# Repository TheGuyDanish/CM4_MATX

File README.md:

# CM4 MATX

## This project has been archived.

Due to a few different reasons, I have decided to archive this project. There's a few different reasons, but mainly that I don't think the CM4 is an appropriate platform for this kind of board. The CPU doesn't really have enough power to utilize the kind of IO that this board would provide it with, combined with the different limitations of using PCI-e switches. This, combined with the fact that I don't have as much time as I'd like to spend on this project, I've decided to leave it be for now.

I'm not aware at the time of writing of any similar projects, but I'll be leaving this one up for folks to take resources and inspiration from.

The original readme is below for archival purposes. So long, thanks for all the fish, and may you have the best of luck in your projects!

/TheGuyDanish

<hr />

Welcome! CM4 MATX is a project aiming to create an open source, micro-ATX standard-compliant motherboard for the Raspberry Pi Compute Module 4.

<p align="center"></p>

The intent behind this is to provide a motherboard that can be installed in a regular case, as well as provide more, or easier access to, potential IO, as well as using a standard 24-pin ATX power supply. This project uses much of the CM4 IO board as its reference design, with new features added onto the board.

The current design goals are as follows:
* Use a standard mATX form factor (244*244mm) and mounting holes
* Provide dual rear-panel USB ports via USB2514B/M2 USB Hub
* Provide an internal USB expansion header for front-panel USB ports
* Provide a standard gigabit Ethernet interface for the rear panel
* Provide stacked dual HDMI outputs on the rear panel
* Provide stacked dual HDMI inputs on the rear panel, with the aid of the Toshiba TC358743 CSI2-to-HDMI bridge IC
* Where reasonably possible, expose the dual DSI headers
* Provide rear-panel acess to other RPI staples, such as SD card and 40-pin GPIO headers
* Via the PI7C9X2G404SL PCI-e switch IC, provide three lanes of PCI-e Gen 2.0 to host multiple expansion cards. These will be x16 slots, wired x1 electrically, to reduce the need for adapters
* Via the PI3PCIE2215 PCI-e mux IC, offer the user the choice between a physical PCI-e slot, or an NVMe slot using one of the downstream PCI-e lanes from the above switch.

# Help Wanted

Update: We have reached a state where we feel comfortable beginning to route the different features of the board. If you have experience with routing PCBs, you are very welcome to download the Kicad files and have a look for yourself. If you have any questions, feel free to join us on Discord if you have any questions and would like to reach out to me directly!

I (TheGuyDanish) am not an experienced board designer, nor a whiz at electronic schematics. That's why I am posting this to Github. I'd love for other hobbyists to join this project. Not just to correct my inevitable mistakes, but also to suggest new features that would make this board even better.

For technical specifics, the KiCad project was made in version 5.1.8 stable. All components not found in the standard KiCad library are included in the CM4_MATX.pretty folder (PCB footprints) and CM4_MATX.lib (schematic symbols) file.

Please see CONTRIBUTING.md for more information!

If you have the technical skills to improve this schematic, I do implore you to make a copy of the repository, make your changes and submit them in a pull request.

If you have ideas you would like to add to the design goals, please submit them in an issue so they can be discussed.

Lastly, huge thanks to volkertb, UnKnoWn-Consortium, mo-g and geerlingguy for the discussion of this in https://github.com/geerlingguy/raspberry-pi-pcie-devices/issues/19 that spawned this effort.

# License

NOTE: Some models, schematics, and/or footprints, are provided by individual manufacturers. As such, all terms and conditions for use, as well as licensing, falls to these original manufacturers. For more information, please inquire with the original component manufacturer or raise an issue here.

Copyright Oliver Møller/[@TheGuyDanish](https://github.com/TheGuyDanish) 2020.

This source describes Open Hardware and is licensed under the CERN-OHL-P v2

You may redistribute and modify this documentation and make products
using it under the terms of the CERN-OHL-P v2 (https:/cern.ch/cern-ohl).
This documentation is distributed WITHOUT ANY EXPRESS OR IMPLIED
WARRANTY, INCLUDING OF MERCHANTABILITY, SATISFACTORY QUALITY
AND FITNESS FOR A PARTICULAR PURPOSE. Please see the CERN-OHL-P v2
for applicable conditions

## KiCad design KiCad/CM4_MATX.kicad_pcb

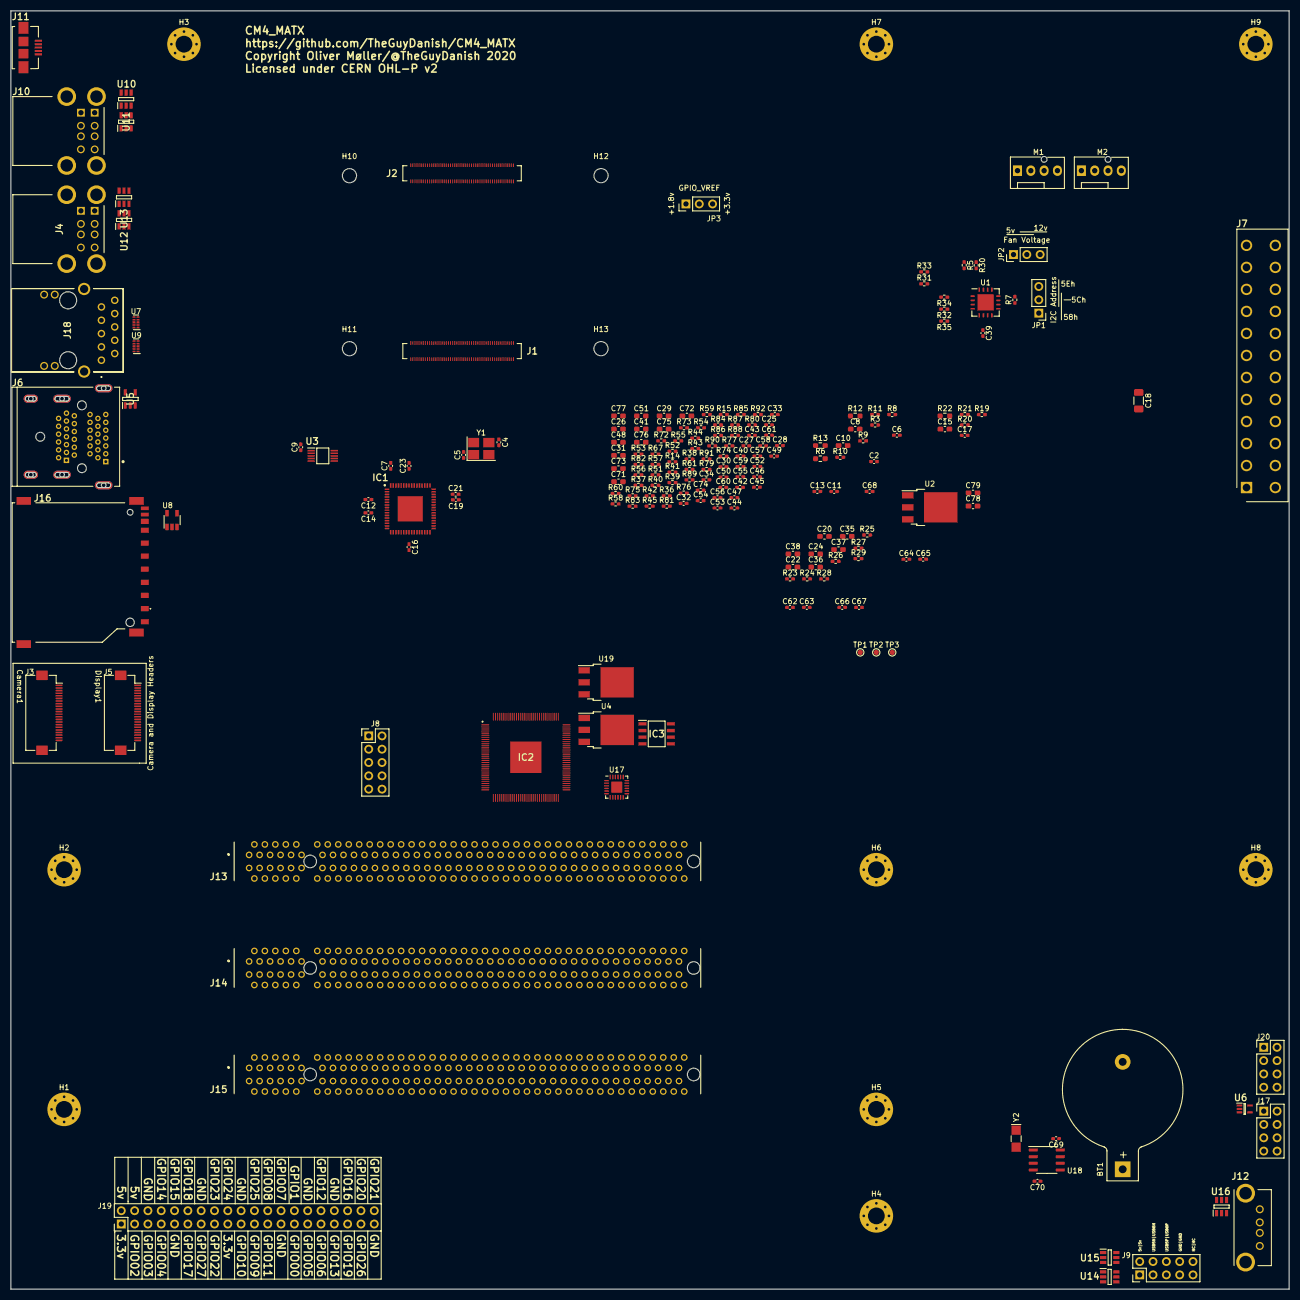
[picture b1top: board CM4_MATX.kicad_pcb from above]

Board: 4 copper layers, 243.8 x 243.8 mm, 214 parts (0 on the bottom side), 283 nets, no tracks yet.

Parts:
BT1: Battery_Cell; BatteryHolder_Keystone_103_1x20mm
C2, C6, C7, C9, C11, C12, C13, C14, C16, C17, C19, C21, C23, C25, C27, C28, C30, C32, C33, C34, C39, C40, C42, C43, C44, C45, C46, C47, C49, C50, C52, C53, C54, C55, C56, C57, C58, C59, C60, C61, C62, C63, C64, C65, C66, C67, C68, C69, C70, C74: 100nF; C_0402_1005Metric_Pad0.74x0.62mm_HandSolder
C4, C5: 16pF; C_0402_1005Metric_Pad0.74x0.62mm_HandSolder
C8, C10, C15, C20, C22, C24, C26, C29, C31, C35, C36, C37, C38, C41, C48, C51, C71, C72, C73, C75, C76, C77, C78, C79: 10uF; C_0603_1608Metric_Pad1.08x0.95mm_HandSolder
C18: 100uF; C_1206_3216Metric_Pad1.33x1.80mm_HandSolder
H1, H2, H3, H4, H5, H6, H7, H8, H9: MountingHole; MountingHole_3.2mm_M3_Pad_Via
H10, H11, H12, H13: MountingHole; MountingHole_2.7mm_M2.5
IC1: USB2517-JZX; QFN50P900X900X100-65N-D
IC2: PI7C9X2G404SLBFDE; QFP40P1600X1600X160-129N
IC3: M24C04-RMN6TP; SOIC127P600X175-8N
J1: CM4_B; DF40C100DS04V51_B
J2: CM4_A; DF40C100DS04V51
J3, J5: Conn_01x22_Female; Hirose_FH12-22S-0.5SH_1x22-1MP_P0.50mm_Horizontal
J4, J10: 72309-8014BLF; 723098014BLF
J6: 1888811-1; TE_1888811-1
J7: 39-28-1243; SHDR24W125P550X420_2X12_5160X960X1310P
J8, J9: Conn_02x05_Odd_Even; PinHeader_2x05_P2.54mm_Vertical
J11: 10104110-0001LF; 101041100001LF
J12: SS-52100-002; SS52100002
J13, J14, J15: PCIe_x16; 10018783-10113TLF
J16: GSD090012SEU
J17, J20: Conn_02x04_Odd_Even; PinHeader_2x04_P2.54mm_Vertical
J18: ARJM11C7-502-AB-ER2-T; ARJM11C7502ABER2T
J19: Conn_02x20_Odd_Even; PinHeader_2x20_P2.54mm_Vertical
JP1, JP2, JP3: Jumper_3_Open; PinHeader_1x03_P2.54mm_Vertical
M1, M2: Fan_CPU_4pin; FanPinHeader_1x04_P2.54mm_Vertical
R3, R8, R9, R10, R11: 100K 5%; R_0402_1005Metric_Pad0.72x0.64mm_HandSolder
R5, R7, R30, R31, R32, R33, R34, R35: 4.7K; R_0402_1005Metric_Pad0.72x0.64mm_HandSolder
R6, R22: 12K 1%; R_0603_1608Metric_Pad0.98x0.95mm_HandSolder
R12, R13: 2.2K 1%; R_0603_1608Metric_Pad0.98x0.95mm_HandSolder
R14: 475 1%; R_0402_1005Metric_Pad0.72x0.64mm_HandSolder
R15: 1.43k 1%; R_0402_1005Metric_Pad0.72x0.64mm_HandSolder
R19: 1K 1%; R_0402_1005Metric_Pad0.72x0.64mm_HandSolder
R20, R21: 470 1%; R_0402_1005Metric_Pad0.72x0.64mm_HandSolder
R23, R24, R25, R26, R27, R28, R29: 143 1%; R_0402_1005Metric_Pad0.72x0.64mm_HandSolder
R36, R37, R38, R39, R40, R73, R74, R75, R76, R77, R79, R80, R81, R82: 330; R_0402_1005Metric_Pad0.72x0.64mm_HandSolder
R41, R42, R43, R44, R45, R51, R52, R53, R67, R72, R91, R92: 5.1k; R_0402_1005Metric_Pad0.72x0.64mm_HandSolder
R54, R55, R56, R57, R58, R59, R60, R61: 33; R_0402_1005Metric_Pad0.72x0.64mm_HandSolder
R83, R84, R85, R86, R87, R88, R89, R90: 49.9; R_0402_1005Metric_Pad0.72x0.64mm_HandSolder
TP1: STATUS2; TestPoint_Pad_D1.0mm
TP2: STATUS0; TestPoint_Pad_D1.0mm
TP3: STATUS1; TestPoint_Pad_D1.0mm
U1: MAX6639ATE+; TQFN-16-1EP_5x5mm_P0.8mm_EP3.1x3.1mm
U2: AP7363-33D; TO-252-3_TabPin2
U3: FSUSB42MUX; SOP50P490X110-10N
U4, U19: AP7363-10D; TO-252-3_TabPin2
U5: AP2822CKETR-G1; SOT95P282X145-5N
U6: 74LVC1G07GW; SOT65P212X110-5N
U7, U9: TPD4EUSB30; USON-10_2.5x1.0mm_P0.5mm
U8: RT9742GGJ5; TSOT-23-5
U10, U11, U12, U13, U14, U15, U16: MIC2019YM6-TR; SOT95P280X145-6N
U17: TCA9548ARGER; Texas_RGE0024C_EP2.1x2.1mm
U18: PCF85263AT; SO-8_3.9x4.9mm_P1.27mm
Y1: 24MHz; Crystal_SMD_3225-4Pin_3.2x2.5mm_HandSoldering
Y2: 32.768KHz; Crystal_SMD_MicroCrystal_CC7V-T1A-2Pin_3.2x1.5mm_HandSolder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

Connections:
+3.3VA: C51.1, C57.1, C76.1, C79.1, IC2.15, J13.B10, J14.B10, J15.B10, U2.3, U19.1
+3.3VP: C68.1, J8.1, J13.A9, J13.A10, J13.B8, J14.A9, J14.A10, J14.B8, J15.A9, J15.A10, J15.B8, U17.21
+3V3: C7.1, C8.1, C9.1, C10.1, C12.1, C14.1, C16.1, C19.1, C21.1, C23.1, C26.1, C29.1, C32.1, C39.1, C40.1, C41.1, C44.1, C45.1, C48.1, C49.1, C50.1, C55.1, C56.1, C58.1, C72.1, C74.1, IC1.5, IC1.10, IC1.24, IC1.52, IC1.57, IC1.64, IC2.1, IC2.8, IC2.49, IC2.64, IC2.79, IC2.82, IC2.84, IC2.96, IC2.113, IC3.8, J3.22, J5.22, J7.2, J7.12, J7.13, JP1.3, R7.2, R32.2, R34.2, R35.2, R41.2, R42.2, R43.2, R44.2, R45.2, R51.1, R52.1, R53.1, R67.2, R72.2, R91.1, R92.1, U1.6, U3.1, U4.1
+12P: J13.A2, J13.A3, J13.B1, J13.B2, J13.B3, J14.A2, J14.A3, J14.B1, J14.B2, J14.B3, J15.A2, J15.A3, J15.B1, J15.B2, J15.B3
+12V: J7.10, J7.11, JP2.3
/+5v: C11.1, C18.1, C20.1, C22.1, C24.1, C35.1, C36.1, C37.1, C38.1, C69.1, J2.77, J7.4, J7.6, J7.21, J7.22, J7.23, J19.2, J19.4, JP2.1, U5.4, U5.5, U10.1, U11.1, U12.1, U13.1, U14.1, U15.1, U16.1, U18.8
/+5vSB: C78.1, J7.9, U2.1
/CAM_GPIO: J2.97, J3.17
/CM4_GPIO/+1.8v: J2.88, J2.90, JP3.1
/CM4_GPIO/+3.3v: J2.84, J2.86, J18.L1, J18.L3, J19.1, J19.17, JP3.3, R22.1, U6.5, U8.5
/CM4_GPIO/BT_nDis: J2.91, J20.3
/CM4_GPIO/EEPROM_nWP: J2.20, J20.7
/CM4_GPIO/ETH_LEDG: J2.15, R20.1
/CM4_GPIO/ETH_LEDY: J2.17, R21.1
/CM4_GPIO/FP_PLED: R19.1, U6.4
/CM4_GPIO/GPIO2: J2.58, J19.3
/CM4_GPIO/GPIO3: J2.56, J19.5
/CM4_GPIO/GPIO4: J2.54, J19.7
/CM4_GPIO/GPIO5: J2.34, J19.29
/CM4_GPIO/GPIO6: J2.30, J19.31
/CM4_GPIO/GPIO7: J2.37, J19.26
/CM4_GPIO/GPIO8: J2.39, J19.24
/CM4_GPIO/GPIO9: J2.40, J19.21
/CM4_GPIO/GPIO10: J2.44, J19.19
/CM4_GPIO/GPIO11: J2.38, J19.23
/CM4_GPIO/GPIO12: J2.31, J19.32
/CM4_GPIO/GPIO13: J2.28, J19.33
/CM4_GPIO/GPIO14: J2.55, J19.8
/CM4_GPIO/GPIO15: J2.51, J19.10
/CM4_GPIO/GPIO16: J2.29, J19.36
/CM4_GPIO/GPIO17: J2.50, J19.11
/CM4_GPIO/GPIO18: J2.49, J19.12
/CM4_GPIO/GPIO19: J2.26, J19.35
/CM4_GPIO/GPIO20: J2.27, J19.38
/CM4_GPIO/GPIO21: J2.25, J19.40
/CM4_GPIO/GPIO22: J2.46, J19.15
/CM4_GPIO/GPIO23: J2.47, J19.16
/CM4_GPIO/GPIO24: J2.45, J19.18
/CM4_GPIO/GPIO25: J2.41, J19.22
/CM4_GPIO/GPIO26: J2.24, J19.37
/CM4_GPIO/GPIO27: J2.48, J19.13
/CM4_GPIO/PI_nLED_ACT: J2.21, J17.3
/CM4_GPIO/RUN_PG: J2.92, J17.7
/CM4_GPIO/SD_CLK: J2.57, J16.5
/CM4_GPIO/SD_CMD: J2.62, J16.2
/CM4_GPIO/SD_DAT0: J2.63, J16.7
/CM4_GPIO/SD_DAT1: J2.67, J16.8
/CM4_GPIO/SD_DAT2: J2.69, J16.9
/CM4_GPIO/SD_DAT3: J2.61, J16.1
/CM4_GPIO/SD_DET: J2.76, J16.10
/CM4_GPIO/SD_PWR: C15.1, J16.4, U8.1
/CM4_GPIO/SD_PWR_ON: J2.75, R22.2, U8.4
/CM4_GPIO/TRD0_N: J2.10, J18.2, U7.4
/CM4_GPIO/TRD0_P: J2.12, J18.1, U7.5
/CM4_GPIO/TRD1_N: J2.6, J18.4, U7.2
/CM4_GPIO/TRD1_P: J2.4, J18.3, U7.1
/CM4_GPIO/TRD2_N: J2.9, J18.8, U9.4
/CM4_GPIO/TRD2_P: J2.11, J18.7, U9.5
/CM4_GPIO/TRD3_N: J2.5, J18.10, U9.2
/CM4_GPIO/TRD3_P: J2.3, J18.9, U9.1
/CM4_GPIO/WL_nDis: J2.89, J20.1
/CM4_GPIO/nPWR_LED: J2.95, U6.2
/CM4_GPIO/nRPIBOOT: J2.93, J20.5
/CM4_HighSpeed/CAM1_C_N: J1.127, J3.8
/CM4_HighSpeed/CAM1_C_P: J1.129, J3.9
/CM4_HighSpeed/CAM1_D0_N: J1.115, J3.2
/CM4_HighSpeed/CAM1_D0_P: J1.117, J3.3
/CM4_HighSpeed/CAM1_D1_N: J1.121, J3.5
/CM4_HighSpeed/CAM1_D1_P: J1.123, J3.6
/CM4_HighSpeed/CAM1_D2_N: J1.133, J3.11
/CM4_HighSpeed/CAM1_D2_P: J1.135, J3.12
/CM4_HighSpeed/CAM1_D3_N: J1.139, J3.14
/CM4_HighSpeed/CAM1_D3_P: J1.141, J3.15
/CM4_HighSpeed/DSI1_C_N: J1.187, J5.8
/CM4_HighSpeed/DSI1_C_P: J1.189, J5.9
/CM4_HighSpeed/DSI1_D0_N: J1.175, J5.2
/CM4_HighSpeed/DSI1_D0_P: J1.177, J5.3
/CM4_HighSpeed/DSI1_D1_N: J1.181, J5.5
/CM4_HighSpeed/DSI1_D1_P: J1.183, J5.6
/CM4_HighSpeed/DSI1_D2_N: J1.193, J5.11
/CM4_HighSpeed/DSI1_D2_P: J1.195, J5.12
/CM4_HighSpeed/DSI1_D3_N: J1.194, J5.14
/CM4_HighSpeed/DSI1_D3_P: J1.196, J5.15
/CM4_HighSpeed/HDMI0_CEC: J1.151, J6.AP13
/CM4_HighSpeed/HDMI0_CK_N: J1.190, J6.AP12
/CM4_HighSpeed/HDMI0_CK_P: J1.188, J6.AP10
/CM4_HighSpeed/HDMI0_D0_N: J1.184, J6.AP9
/CM4_HighSpeed/HDMI0_D0_P: J1.182, J6.AP7
/CM4_HighSpeed/HDMI0_D1_N: J1.178, J6.AP6
/CM4_HighSpeed/HDMI0_D1_P: J1.176, J6.AP4
/CM4_HighSpeed/HDMI0_D2_N: J1.172, J6.AP3
/CM4_HighSpeed/HDMI0_D2_P: J1.170, J6.AP1
/CM4_HighSpeed/HDMI0_HOTPLUG: J1.153, J6.AP19
/CM4_HighSpeed/HDMI0_SCL: J1.200, J6.AP15
/CM4_HighSpeed/HDMI0_SDA: J1.199, J6.AP16
/CM4_HighSpeed/HDMI1_CEC: J1.149, J6.BP13
/CM4_HighSpeed/HDMI1_CK_N: J1.166, J6.BP12
/CM4_HighSpeed/HDMI1_CK_P: J1.164, J6.BP10
/CM4_HighSpeed/HDMI1_D0_N: J1.160, J6.BP9
/CM4_HighSpeed/HDMI1_D0_P: J1.158, J6.BP7
/CM4_HighSpeed/HDMI1_D1_N: J1.154, J6.BP6
/CM4_HighSpeed/HDMI1_D1_P: J1.152, J6.BP4
/CM4_HighSpeed/HDMI1_D2_N: J1.148, J6.BP3
/CM4_HighSpeed/HDMI1_D2_P: J1.146, J6.BP1
/CM4_HighSpeed/HDMI1_HOTPLUG: J1.143, J6.BP19
/CM4_HighSpeed/HDMI1_SCL: J1.147, J6.BP15
/CM4_HighSpeed/HDMI1_SDA: J1.145, J6.BP16
/CM4_HighSpeed/HDMI_5v: C13.1, J6.AP18, J6.BP18, U5.1
/CM4_HighSpeed/PCIE_CLK_N: IC2.73, J1.112
/CM4_HighSpeed/PCIE_CLK_P: IC2.74, J1.110
/CM4_HighSpeed/PCIE_NRST: IC2.10, J1.109
/CM4_HighSpeed/PCIE_RX_N: IC2.123, J1.118
/CM4_HighSpeed/PCIE_RX_P: IC2.124, J1.116
/CM4_HighSpeed/USB2_N: J1.103, U3.4
/CM4_HighSpeed/USB2_P: J1.105, U3.3
/CM4_USB2_Power/HD1_5v: J10.A1, U10.6
/CM4_USB2_Power/HD2_5v: J10.B1, U11.6
/CM4_USB2_Power/HD3_5v: J4.A1, U12.6
/CM4_USB2_Power/HD4_5v: J4.B1, U13.6
/CM4_USB2_Power/HD5_5v: J9.1, U14.6
/CM4_USB2_Power/HD6_5v: J9.2, U15.6
/CM4_USB2_Power/HD7_5v: J12.1, U16.6
/CM4_USB2_Power/USB1_PWR: IC1.29, U10.3
/CM4_USB2_Power/USB2_PWR: IC1.26, U11.3
/CM4_USB2_Power/USB3_PWR: IC1.23, U12.3
/CM4_USB2_Power/USB4_PWR: IC1.20, U13.3
/CM4_USB2_Power/USB5_PWR: IC1.30, U14.3
/CM4_USB2_Power/USB6_PWR: IC1.39, U15.3
/CM4_USB2_Power/USB7_PWR: IC1.36, U16.3
/CM4_USB2_Power/nOCS1: IC1.28, U10.4
/CM4_USB2_Power/nOCS2: IC1.27, U11.4
/CM4_USB2_Power/nOCS3: IC1.22, U12.4
/CM4_USB2_Power/nOCS4: IC1.21, U13.4
/CM4_USB2_Power/nOCS5: IC1.35, U14.4
/CM4_USB2_Power/nOCS6: IC1.38, U15.4
/CM4_USB2_Power/nOCS7: IC1.37, U16.4
/FanCTRL_MAX6639/ADD: JP1.2, U1.11
/FanCTRL_MAX6639/DX: U1.8, U1.9, U1.10
/FanCTRL_MAX6639/PWM1: M1.4, R30.2, U1.15
/FanCTRL_MAX6639/PWM2: M2.4, R33.2, U1.1
/FanCTRL_MAX6639/TACH1: M1.3, R5.2, U1.16
/FanCTRL_MAX6639/TACH2: M2.3, R31.2, U1.2
/FanCTRL_MAX6639/V_FAN: JP2.2, M1.2, M2.2, R5.1, R30.1, R31.1, R33.1
/FanCTRL_MAX6639/~ALERT: R7.1, U1.12
/FanCTRL_MAX6639/~FANFAIL: R34.1, U1.3
/FanCTRL_MAX6639/~OT: R35.1, U1.5
/FanCTRL_MAX6639/~THERM: R32.1, U1.4
/GPIO_VREF: J2.78, JP3.2
/ID_SC: J2.35, J19.28
/ID_SD: J2.36, J19.27
/PCIe_Subsystem/PCIE1_SMBUS_CLK: J13.B5, U17.4
/PCIe_Subsystem/PCIE1_SMBUS_DATA: J13.B6, U17.3
/PCIe_Subsystem/PCIE2_SMBUS_CLK: J14.B5, U17.6
/PCIe_Subsystem/PCIE2_SMBUS_DATA: J14.B6, U17.5
/PCIe_Subsystem/PCIE3_SMBUS_CLK: J15.B5, U17.8
/PCIe_Subsystem/PCIE3_SMBUS_DATA: J15.B6, U17.7
/PCIe_Subsystem/PCIESW_SMBUS_CLK: IC2.26, U17.2
/PCIe_Subsystem/PCIESW_SMBUS_DATA: IC2.27, U17.1
/PCIe_Subsystem/PCIE_RX_N: IC2.127, J1.124
/PCIe_Subsystem/PCIE_RX_P: IC2.128, J1.122
/PCIe_Subsystem/PCIE_SW_TCK: IC2.89, J8.4
/PCIe_Subsystem/PCIE_SW_TMS: IC2.92, J8.2
/PCIe_Subsystem/PCIe_Slot1/PCIE1_CLK_N: J13.A14, R57.1, R86.2
/PCIe_Subsystem/PCIe_Slot1/PCIE1_CLK_P: J13.A13, R56.1, R85.2
/PCIe_Subsystem/PCIe_Slot1/PCIE1_PERST: IC2.5, J13.A11, R51.2
/PCIe_Subsystem/PCIe_Slot1/PCIE1_PRSNT: IC2.19, J13.B17
/PCIe_Subsystem/PCIe_Slot1/PCIE1_RX_N: IC2.101, J13.A16
/PCIe_Subsystem/PCIe_Slot1/PCIE1_RX_P: IC2.100, J13.A17
/PCIe_Subsystem/PCIe_Slot1/PCIe_1_TX_N: C65.1, J13.B15
/PCIe_Subsystem/PCIe_Slot1/PCIe_1_TX_P: C64.2, J13.B14
/PCIe_Subsystem/PCIe_Slot2/PCIE2_CLK_N: C62.1, IC2.102, J14.A14, R59.1, R88.2
/PCIe_Subsystem/PCIe_Slot2/PCIE2_CLK_P: J14.A13, R58.1, R87.2
/PCIe_Subsystem/PCIe_Slot2/PCIE2_PERST: IC2.6, J14.A11, R52.2
/PCIe_Subsystem/PCIe_Slot2/PCIE2_PRSNT: IC2.20, J14.B17
/PCIe_Subsystem/PCIe_Slot2/PCIE2_RX_N: IC2.107, J14.A17
/PCIe_Subsystem/PCIe_Slot2/PCIE2_RX_P: IC2.106, J14.A16
/PCIe_Subsystem/PCIe_Slot2/PCIe_2_TX_N: C63.1, J14.B15
/PCIe_Subsystem/PCIe_Slot2/PCIe_2_TX_P: C62.2, J14.B14
/PCIe_Subsystem/PCIe_Slot3/PCIE3_CLK_N: J15.A14, R61.1, R90.2
/PCIe_Subsystem/PCIe_Slot3/PCIE3_CLK_P: J15.A13, R60.1, R89.2
/PCIe_Subsystem/PCIe_Slot3/PCIE3_PERST: IC2.7, J15.A11, R53.2
/PCIe_Subsystem/PCIe_Slot3/PCIE3_PRSNT: IC2.21, J15.B17
/PCIe_Subsystem/PCIe_Slot3/PCIE3_RX_N: IC2.117, J15.A17
/PCIe_Subsystem/PCIe_Slot3/PCIE3_RX_P: IC2.118, J15.A16
/PCIe_Subsystem/PCIe_Slot3/PCIe_3_TX_N: C67.1, J15.B15
/PCIe_Subsystem/PCIe_Slot3/PCIe_3_TX_P: C66.2, J15.B14
/PCIe_Subsystem/PCIe_Switch/+1.0v: C25.1, C27.1, C28.1, C30.1, C31.1, C33.1, C34.1, C42.1, C43.1, C46.1, C47.1, C52.1, C53.1, C59.1, C60.1, C71.1, C75.1, IC2.3, IC2.23, IC2.29, IC2.31, IC2.40, IC2.55, IC2.62, IC2.65, IC2.91, IC2.99, IC2.105, IC2.108, IC2.119, IC2.125, U4.3
/PCIe_Subsystem/PCIe_Switch/+1.0vSB: C54.1, C61.1, C73.1, C77.1, IC2.13, IC2.14, U19.3
/PCIe_Subsystem/PCIe_Switch/CGND: IC2.109, IC2.112
/PCIe_Subsystem/PCIe_Switch/CLKBUF_PD: IC2.60, R82.2
/PCIe_Subsystem/PCIe_Switch/CLKQ0_N: R55.1, R84.2
/PCIe_Subsystem/PCIe_Switch/CLKQ0_P: R54.1, R83.2
/PCIe_Subsystem/PCIe_Switch/EECLK: IC2.70, IC3.6, R91.2
/PCIe_Subsystem/PCIe_Switch/EEPD: IC2.71, IC3.5, R92.2
/PCIe_Subsystem/PCIe_Switch/GPIO0: IC2.36, R36.2
/PCIe_Subsystem/PCIe_Switch/GPIO1: IC2.35, R37.2
/PCIe_Subsystem/PCIe_Switch/GPIO2: IC2.37, R38.2
/PCIe_Subsystem/PCIe_Switch/GPIO3: IC2.38, R39.2
/PCIe_Subsystem/PCIe_Switch/GPIO4: IC2.39, R40.2
/PCIe_Subsystem/PCIe_Switch/IREF: IC2.86, R14.2
/PCIe_Subsystem/PCIe_Switch/PCIE1_RX_N: C65.2, IC2.98
/PCIe_Subsystem/PCIe_Switch/PCIE1_RX_P: C64.1, IC2.97
/PCIe_Subsystem/PCIe_Switch/PCIE2_RX_N: C63.2, IC2.103
/PCIe_Subsystem/PCIe_Switch/PCIE3_RX_N: C67.2, IC2.121
/PCIe_Subsystem/PCIe_Switch/PCIE3_RX_P: C66.1, IC2.122
/PCIe_Subsystem/PCIe_Switch/PL_512B: IC2.53, R81.2
/PCIe_Subsystem/PCIe_Switch/PWR_SAV: IC2.28, R67.1
/PCIe_Subsystem/PCIe_Switch/REXT: IC2.116, R15.2
/PCIe_Subsystem/PCIe_Switch/REXT_GND: IC2.115, R15.1
/PCIe_Subsystem/PCIe_Switch/RXPOLINV_DIS: IC2.24, R76.2
/PCIe_Subsystem/PCIe_Switch/SCAN_EN: IC2.72, R79.2
/PCIe_Subsystem/PCIe_Switch/SLOTCLK: IC2.33, R41.1
/PCIe_Subsystem/PCIe_Switch/SLOT_IMP1: IC2.45, R42.1
/PCIe_Subsystem/PCIe_Switch/SLOT_IMP2: IC2.46, R43.1
/PCIe_Subsystem/PCIe_Switch/SLOT_IMP3: IC2.47, R44.1
/PCIe_Subsystem/PCIe_Switch/TEST1: IC2.9, R45.1
/PCIe_Subsystem/PCIe_Switch/TEST2: IC2.16, R72.1
/PCIe_Subsystem/PCIe_Switch/TEST3: IC2.17, R73.2
/PCIe_Subsystem/PCIe_Switch/TEST4: IC2.22, R75.2
/PCIe_Subsystem/PCIe_Switch/TEST5: IC2.25, R77.2
/PCIe_Subsystem/PCIe_Switch/TEST6: IC2.51, R80.2
/PCIe_Subsystem/PCIe_Switch/VC1_EN: IC2.18, R74.2
/RTC_PCF85263A/OSCI: U18.1, Y2.1
/RTC_PCF85263A/OSCO: U18.2, Y2.2
/RTC_PCF85263A/VBAT: BT1.1, C70.1, U18.3
/SCL0: J2.80, J3.20, J5.20, U1.13, U17.19, U18.6
/SDA0: J2.82, J3.21, J5.21, U1.14, U17.20, U18.5
/USB2_HUB/3.3v: IC1.44, IC1.46
/USB2_HUB/HD1_N: IC1.1, J10.A2
/USB2_HUB/HD1_P: IC1.2, J10.A3
/USB2_HUB/HD2_N: IC1.3, J10.B2
/USB2_HUB/HD2_P: IC1.4, J10.B3
/USB2_HUB/HD3_N: IC1.6, J4.A2
/USB2_HUB/HD3_P: IC1.7, J4.A3
/USB2_HUB/HD4_N: IC1.8, J4.B2
/USB2_HUB/HD4_P: IC1.9, J4.B3
/USB2_HUB/HD5_N: IC1.11, J9.3
/USB2_HUB/HD5_P: IC1.12, J9.5
/USB2_HUB/HD6_N: IC1.53, J9.4
/USB2_HUB/HD6_P: IC1.54, J9.6
/USB2_HUB/HD7_N: IC1.55, J12.2
/USB2_HUB/HD7_P: IC1.56, J12.3
/USB2_HUB/USBH_N: IC1.58, U3.8
/USB2_HUB/USBH_P: IC1.59, U3.9
/USB2_HUB/USBOTG: J1.101, R12.1, R13.2, U3.2
/USB2_HUB/XTAL1: C4.2, IC1.61, Y1.3
/USB2_HUB/XTAL2: C5.1, IC1.60, Y1.1
/nEXTRST: IC1.43, J2.100
GND: BT1.2, C2.2, C4.1, C5.2, C6.2, C7.2, C8.2, C9.2, C10.2, C11.2, C12.2, C13.2, C14.2, C15.2, C16.2, C17.2, C18.2, C19.2, C20.2, C21.2, C22.2, C23.2, C24.2, C25.2, C26.2, C27.2, C28.2, C29.2, C30.2, C31.2, C32.2, C33.2, C34.2, C35.2, C36.2, C37.2, C38.2, C39.2, C40.2, C41.2, C42.2, C43.2, C44.2, C45.2, C46.2, C47.2, C48.2, C49.2, C50.2, C51.2, C52.2, C53.2, C54.2, C55.2, C56.2, C57.2, C58.2, C59.2, C60.2, C61.2, C68.2, C69.2, C70.2, C71.2, C72.2, C73.2, C74.2, C75.2, C76.2, C77.2, C78.2, C79.2, IC1.19, IC1.65, IC2.2, IC2.4, IC2.11, IC2.12, IC2.30, IC2.32, IC2.34, IC2.41, IC2.50, IC2.56, IC2.61, IC2.63, IC2.66, IC2.87, IC2.90, IC2.95, IC2.104, IC2.120, IC2.126, IC2.129, IC3.2, IC3.3, IC3.4, IC3.7, J1.107, J1.108, J1.113, J1.114, J1.119, J1.120, J1.125, J1.126, J1.131, J1.132, J1.137, J1.138, J1.144, J1.150, J1.155, J1.156, J1.161, J1.162, J1.167, J1.168, J1.173, J1.174, J1.179, J1.180, J1.185, J1.186, J1.191, J1.192, J1.197, J1.198, J2.1, J2.2, J2.7, J2.8, J2.13, J2.14, J2.22, J2.23, J2.32, J2.33, J2.42, J2.43, J2.52, J2.53, J2.59, J2.60, J2.65, J2.66, J2.71, J2.74, J2.98, J3.1, J3.4, J3.7, J3.10, J3.13, J3.16, J3.19, J4.A4, J4.B4, J4.MH1, J4.MH2, J4.MH3, J4.MH4, J5.1, J5.4, J5.7, J5.10, J5.13, J5.16, J5.19, J6.AP2, J6.AP5, J6.AP8, J6.AP11, J6.AP17, J6.BP2, J6.BP5, J6.BP8, J6.BP11, J6.BP17, J6.SH1, J6.SH2, J6.SH3, J6.SH4, J6.SH5, J6.SH6, J7.3, J7.5, J7.7, J7.15, J7.17, J7.18, J7.19, J7.24, J8.3, J8.5, J8.9, J9.7, J9.8, J10.A4, J10.B4, J10.MH1, J10.MH2, J10.MH3, J10.MH4, J11.5, J11.MP1, J11.MP2, J11.MP3, J11.MP4, J12.4, J12.MH1, J12.MH2, J13.A1, J13.A4, J13.A12, J13.A15, J13.A18, J13.A20, J13.A23, J13.A24, J13.A27, J13.A28, J13.A31, J13.A34, J13.A37, J13.A38, J13.A41, J13.A42, J13.A45, J13.A46, J13.A49, J13.A51, J13.A54, J13.A55, J13.A58, J13.A59, J13.A62, J13.A63, J13.A66, J13.A67, J13.A70, J13.A71, J13.A74, J13.A75, J13.A78, J13.A79, J13.A82, J13.B4, J13.B7, J13.B13, J13.B16, J13.B18, J13.B21, J13.B22, J13.B25, J13.B26, J13.B29, J13.B30, J13.B32, J13.B35, J13.B36, J13.B39, J13.B40, J13.B43, J13.B44, J13.B47, J13.B49, J13.B52, J13.B53, J13.B56, J13.B57, J13.B60, J13.B61, J13.B64, J13.B65, J13.B68, J13.B69, J13.B72, J13.B73, J13.B76, J13.B77, J13.B80, J14.A1, J14.A4, J14.A12, J14.A15, J14.A18, J14.A20, J14.A23, J14.A24, J14.A27, J14.A28, J14.A31, J14.A34, J14.A37, J14.A38, J14.A41, J14.A42, J14.A45, J14.A46, J14.A49, J14.A51, J14.A54, J14.A55, J14.A58, J14.A59, J14.A62, J14.A63, J14.A66, J14.A67, J14.A70, J14.A71, J14.A74, J14.A75, J14.A78, J14.A79, J14.A82, J14.B4, J14.B7, J14.B13, J14.B16, J14.B18, J14.B21, J14.B22, J14.B25, J14.B26, J14.B29, J14.B30, J14.B32, J14.B35, J14.B36, J14.B39, J14.B40, J14.B43, J14.B44, J14.B47, J14.B49, J14.B52, J14.B53, J14.B56, J14.B57, J14.B60, J14.B61, J14.B64, J14.B65, J14.B68, J14.B69, J14.B72, J14.B73, J14.B76, J14.B77, J14.B80, J15.A1, J15.A4, J15.A12, J15.A15, J15.A18, J15.A20, J15.A23, J15.A24, J15.A27, J15.A28, J15.A31, J15.A34, J15.A37, J15.A38, J15.A41, J15.A42, J15.A45, J15.A46, J15.A49, J15.A51, J15.A54, J15.A55, J15.A58, J15.A59, J15.A62, J15.A63, J15.A66, J15.A67, J15.A70, J15.A71, J15.A74, J15.A75, J15.A78, J15.A79, J15.A82, J15.B4, J15.B7, J15.B13, J15.B16, J15.B18, J15.B21, J15.B22, J15.B25, J15.B26, J15.B29, J15.B30, J15.B32, J15.B35, J15.B36, J15.B39, J15.B40, J15.B43, J15.B44, J15.B47, J15.B49, J15.B52, J15.B53, J15.B56, J15.B57, J15.B60, J15.B61, J15.B64, J15.B65, J15.B68, J15.B69, J15.B72, J15.B73, J15.B76, J15.B77, J15.B80, J16.3, J16.6, J16.MP1, J16.MP2, J16.MP3, J16.MP4, J17.2, J17.4, J17.6, J17.8, J18.MH1, J18.MH2, J19.6, J19.9, J19.14, J19.20, J19.25, J19.30, J19.34, J19.39, J20.2, J20.4, J20.6, J20.8, JP1.1, M1.1, M2.1, R3.2, R6.1, R8.2, R9.2, R10.2, R11.2, R12.2, R14.1, R23.2, R24.2, R25.2, R26.2, R27.2, R28.2, R29.2, R36.1, R37.1, R38.1, R39.1, R40.1, R73.1, R74.1, R75.1, R76.1, R77.1, R79.1, R80.1, R81.1, R82.1, R83.1, R84.1, R85.1, R86.1, R87.1, R88.1, R89.1, R90.1, U1.7, U2.2, U3.5, U3.10, U4.2, U5.2, U6.3, U7.3, U7.8, U8.2, U9.3, U9.8, U10.2, U11.2, U12.2, U13.2, U14.2, U15.2, U16.2, U17.9, U17.18, U17.22, U17.23, U18.4, U19.2, Y1.2, Y1.4
unnamed: C2.1, IC1.62
unnamed: C6.1, IC1.25
unnamed: C17.1, J18.5, J18.6
unnamed: IC1.13, R3.1
unnamed: IC1.40, R8.1
unnamed: IC1.41, R9.1
unnamed: IC1.42, R10.1
unnamed: IC1.45, R11.1
unnamed: IC1.63, R6.2
unnamed: IC2.67, TP2.1
unnamed: IC2.68, TP3.1
unnamed: IC2.69, TP1.1
unnamed: IC2.75, R61.2
unnamed: IC2.76, R60.2
unnamed: IC2.77, R59.2
unnamed: IC2.78, R58.2
unnamed: IC2.80, R57.2
unnamed: IC2.81, R56.2
unnamed: IC2.83, R55.2
unnamed: IC2.85, R54.2
unnamed: J2.85, J2.87
unnamed: J11.1, R13.1
unnamed: J11.2, U3.6
unnamed: J11.3, U3.7
unnamed: J17.1, R19.2
unnamed: J18.L2, R20.2
unnamed: J18.L4, R21.2
unnamed: R23.1, U10.5
unnamed: R24.1, U11.5
unnamed: R25.1, U12.5
unnamed: R26.1, U13.5
unnamed: R27.1, U14.5
unnamed: R28.1, U15.5
unnamed: R29.1, U16.5

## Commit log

2020-11-14 Big changes (see expanded comment)
    Added new components:
    USB2517-JZX USB2.0 Hub
    SI-52100-002 Vertical USB2.0 A Header
    Began work on USB schematic, mostly done. Needs power delivery work done
2020-11-14 Added contributing documentation.
2020-11-15 placed mounting holes as per specification
    (0,0) on top left
2020-11-15 Preliminary component placement and PCB PDF
2020-11-16 Issue #12: Add picture to README to spice things up.
2020-11-16 added symbol for MAX6615
2020-11-16 added footprints (SMD 0805, MAX6615)
2020-11-17 added footprint for connector
2020-11-17 reworked footprint of MAX6615
2020-11-17 added CM4_FanCRTL schematic
2020-11-17 added CM4_FanCRTL to CM4_MATX
2020-11-19 Where do I even start...
    Rebasing the entire project to use KiCad 5.1.8 stable instead of nightly.
    Most of the progress made on the schematic still in place, with a few exceptions that I can handle over the next few days.
    Additonally. Resolves #17, #19, and parts of #18 (I still want to build some automated checks into the project once we are at a more advanced state)
2020-11-19 removed old footprint library
2020-11-19 added mounting holes to CM4_MATX.sch
2020-11-19 added pcb dimensions and mounting holes
2020-11-19 fixed missplaced mountinghole H3
2020-11-19 added rear io window placeholder
2020-11-19 changed page size to A3
2020-11-21 Lotsa changes
    Added new footprints:
    PCIe x1, TO-252 tab, SOT95, SOP50, SON50, Hirose FH-12-22S, 2.54mm 2x02 and 2x05 headers
    Added new models:
    Hirose FH-12-22S, FSUSB42MUX, MIC2019YM6-TR, TPS6206
    Re-did ATX connector symbol wiring
    Begun wiring PI7C PCI-e switch
2020-11-22 Re-added PCB preview image
2020-11-22 Clean up references to _LibLoader library
2020-11-22 Added a full-size SD card slot to help solve #4
2020-11-22 added FanCRTL with MAX31740 as hierarchical sheet
    with all footprints and symbols necessary
2020-11-22 reworked descriptive text to be more precise
2020-11-22 added FanCRTL with MAX6615 as hierarchical sheet
    and all its footprints and symbols
2020-11-22 added some NC flags
2020-11-22 replaced wrong GND symbol
2020-11-22 added net names to schematic
2020-11-22 updated MAX6615 footprint
2020-11-22 placed components as a functional group
2020-11-22 updated symbol and footprint of MAX31740
2020-11-22 updated schematic
2020-11-22 added FanCRTL with EMC2302 as hierarchical sheet
    and all necessary footprints and symbols
2020-11-22 changed referenced footprint on fan header
2020-11-22 changed referenced footprint of fan header
2020-11-23 Add 3D rendering of PCB. 3D rendering created by exporting from KiCad to VRML format, and importing it in Blender 2.79 (later versions ignore color on VRML import) NOTE: KiCad->VRML->Blender export/i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
    See issue TheGuyDanish/CM4_MATX#14
2020-11-24 Many, many changes...
    Added a bunch of new footprints and a couple of new symbols.
    Added the other side of the CM4 connector and wired its features.
    Added some more detailed models for a fair few components.
    Added a new schematic to handle power for USB ports.
    Updated the PCB with the new components and moved some around to populate the rear IO panel.
2020-11-25 Added a new 3.3V-1.0V regulator
    (I was intending for this to be part of a bigger commit where I finally fix the PI7C power delivery, but it proved a little too daunting for the moment.)
2020-11-27 Small changes to PCIe, USB Schematics and board layout, legend for GPIO pins.
2020-12-14 Added License text, fixes #30, updated PCB to include copyright notice.
2020-12-14 Added updated PCB PDF and image
2020-12-18 fixed mounting holes
2020-12-19 Updating PCIe symbols + PCIe power stub sheet
2020-12-20 Updated schematic PDF and re-did PSU-PCIe_PWR connections
2020-12-20 updated dimensions
    begin of dimensional chain for the board is the bottom left corner at X1.5 Y10.5
2020-12-20 updated pcb image
2020-12-20 Moved J13-15 to fix overlap
2020-12-22 Updated PCI-e switch with more power wiring
    Still needs more work on connectivity before #28 can be solved.
2020-12-22 Updated schematic preview PDF
2020-12-23 added needed footprints and symbols
    R0805, C0805, Solder-Jumper, TQFN-16, GND and Fan-Pinheader
2020-12-23 added schematic of FanCTRL with MAX6639
2020-12-23 placed footprints on pcb as a functional group
2020-12-23 generated part numbering
2020-12-23 updated printouts of schematics and pcb
2020-12-23 updated sheet numeration of schematic files
2020-12-23 changed solder jumper to pin jumper
2020-12-23 updated schematic and pcb printouts
2020-12-23 added jumper descriptions
2020-12-24 added QFN16 5x5mm 3D model
2020-12-24 changed file name to *.stp
    to match the other files
2020-12-24 Replaced Ethernet connector and removed unnecessary files
    Fixes #38
2020-12-24 Corrected library the ARJM11C7 schematic is loaded from
2020-12-25 edited origin of pcie connector footprint
    for better aligning and measuring (no mixing of mm and in) on pcb
2020-12-25 moved pcie connectors to location
    as per https://www.silverstonetek.com/techtalk/11008/pic-7.png
2020-12-25 locked mounting holes and pcie connectors
    as they are dependent on each others position
2020-12-25 renumbered erroring net
2020-12-25 Updated README to clarify licensing terms for components
2020-12-25 Updated PCB preview imagery
2020-12-27 fixed 3D settings of PCIe footprints
2020-12-28 Added 3.3v standby voltage regulator for PCI-e auxiliary power
2020-12-28 First CI test - #44
2020-12-28 Updated LICENSE
2020-12-28 More CI testing (Sorry)
2020-12-28 (Yet another) Update kicad.yml
2020-12-28 CI Test - Round three
2020-12-28 More CI Changes
2020-12-28 CI Test
2020-12-28 added jumper for GPIO_VREF selection
2020-12-28 updated part numerations
2020-12-30 Adding PCIe subsystem
    - Moves a lot of the PCIe related items from the top level sheet to a new sheet called PCIe Subsystem which then has other hierarchical sheets below it.
    - This adds some of the AC coupling caps for the PCIe slots, might need to do some work with the switch yet.
    - Adds an SMBUS mux for the SMBUS connections to the PCIe slots. Extra SMBUS lanes sit un-wired and can be used for other things.
    - Adds JTAG headers for the PCIe connectors.
2021-01-03 added hierarchical sheet for rtc
2021-01-03 added PCF85263A symbol and footprint to project library
2021-01-03 added battery and crystal footprints to library
2021-01-03 added RTC circuit
2021-01-03 updated PCB with RTC circuit
2021-01-03 updated PDFs and JPG
2021-01-03 added 3D model of SO-8
    source https://www.3dcontentcentral.com/secure/download-model.aspx?catalogid=1023&id=72
2021-01-03 added 3D model of crystal
    source: https://www.3dcontentcentral.com/secure/download-model.aspx?catalogid=171&id=289153
2021-01-03 fixed 3D model offset of PCIe slots
2021-01-06 removed i2c pull-up resistors to +5v
2021-01-07 Removing Display0 and Camera0
    Eliminates the need for J1, R1 and R2. Also removed.
2021-01-07 Tons of wiring and pin straps for PCI-e Switch
    Also re-did some hierarchical labels for JTAG
2021-01-07 Updated schematic PDF
2021-01-07 Added second USB dual-stack header and fixed some library references.
2021-01-07 Updated preview files
2021-01-10 fixed pin1 marker on ARJM connector
    it broke the wrl export for later rendering
2021-01-18 PCIe Wiring, resistor value adjustments, and a bunch of small ERC fixes.
2021-01-18 Updated schematic for fdb83ae
2021-02-08 Updated CM4 footprints/symbols, mounting holes
    This is in a bid to make it more manufactuerable by reducing the need for explanations and questions.
2021-02-08 Added buffering caps to U2 (3.3vSB provider)
2021-03-01 Started picking passive components, overhauled library
    Cleaned up a bunch of schematic library references.
    Added datasheets, descriptions for a lot of existing parts.
    Picked most capacitor parts, still a couple left.
    Cleaned up a fair few footprint references.
2021-03-03 Updated Y1 capacitors
2021-03-03 Removed R4
2021-03-03 Moved C4 and C5 in the schematic to be more logical
2021-03-03 More BOM detailing and small changes
    Removed some NC components from the PCI-e subsection
    Picked resistor footprints
    Picked resistor items in the BOM
2021-03-03 More BOM changes
2021-03-03 Imported new components to the PCB and moved some components
    Updated PDFs and added two new board layers. One for ground and a second for power (voltage to be decided)
2021-03-03 Updated schematic date and PCB preview image
2021-03-13 Added some DRC specifics
2021-05-28 Connected all grounds in the schematic and planes
    Planes:
    In 1 - Ground
    In 2 - 3.3v Zone which excludes the IO and 5v Zone around only the IO
2021-05-28 Removed Autosave
2021-05-28 Added autosaves to git ignore
    People should save stuff properly
2021-05-28 Added Planes
2021-05-28 Added MoBo standoff exclusion zones
2021-05-28 CI workflow changes
    Disable automatic 3D model generation due to some difficulty in getting KiCad-standard library 3D models.
    Added In1.Cu and In2.Cu to Gerber output
    Created a separate layer PDF artifact for each PCB layer (should till be put into one zip file)
2021-05-28 More CI fixing/testing
2021-05-28 More more CI testing
2022-08-10 Add .gitattributes

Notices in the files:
KiCad/CM4_MATX.kicad_pcb:
Copyright Oliver Møller/@TheGuyDanish 2020
Licensed under CERN OHL-P v2
